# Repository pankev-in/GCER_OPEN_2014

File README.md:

GCER_OPEN_2014
==============

GCER OPEN GAME 2014

Concept:
	-Mechanical:
		two arms, one to hang the hangers on to the Rack,and another one will just attack opponents' side rack

	-Electronic+Controller:
		2 different voltage regulator:
			8V for motors and controller
			5V for Servos
		using Arduino Mega 2560 as the low level communication processor to controll ther hardware
		Raspberry Pi for extential programming tool or other

Game flow:
	1. Robot adjust at frist in the Starting box with hangers on the Robot.
	2. Drive directly to the Side Rack and hang those two hangers on it.
	3. Return to the black tape and turn left to adjust the position.
	4. Drive ahead to the Center Rack and get the other hangers.
	5. Back to Side Rack and put hangers on it.
	... Repeating...
	?. Drive direct to the Opponents' side 
	?. turn around and distroy them XD(Better with some mario musik~).

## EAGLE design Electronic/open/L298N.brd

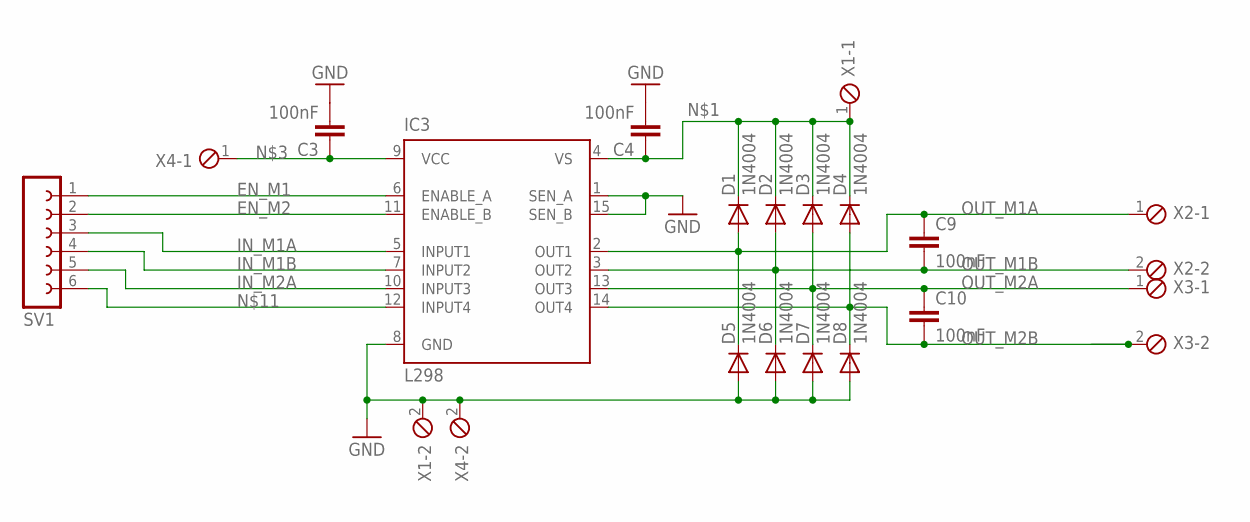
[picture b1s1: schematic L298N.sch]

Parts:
C3, C4, C9, C10: 100nF; C050-050X075
D1, D2, D3, D4, D5, D6, D7, D8: 1N4004; DO41-10
IC3: L298; MULTIWATT-15
SV1: FE06-1; FE06
X1, X2, X3, X4: MPT2; 2POL254

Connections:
EN_M1: IC3.6 (ENABLE_A), SV1.1
EN_M2: IC3.11 (ENABLE_B), SV1.2
GND: C3.2, C4.2, D5.A, D6.A, D7.A, D8.A, IC3.1 (SEN_A), IC3.8 (GND), IC3.15 (SEN_B), X1.2, X4.2
IN_M1A: IC3.5 (INPUT1), SV1.3
IN_M1B: IC3.7 (INPUT2), SV1.4
IN_M2A: IC3.10 (INPUT3), SV1.5
unnamed: C4.1, D1.C, D2.C, D3.C, D4.C, IC3.4 (VS), X1.1
unnamed: C3.1, IC3.9 (VCC), X4.1
unnamed: IC3.12 (INPUT4), SV1.6
OUT_M1A: C9.1, D1.A, D5.C, IC3.2 (OUT1), X2.1
OUT_M1B: C9.2, D2.A, D6.C, IC3.3 (OUT2), X2.2
OUT_M2A: C10.1, D3.A, D7.C, IC3.13 (OUT3), X3.1
OUT_M2B: C10.2, D4.A, D8.C, IC3.14 (OUT4), X3.2

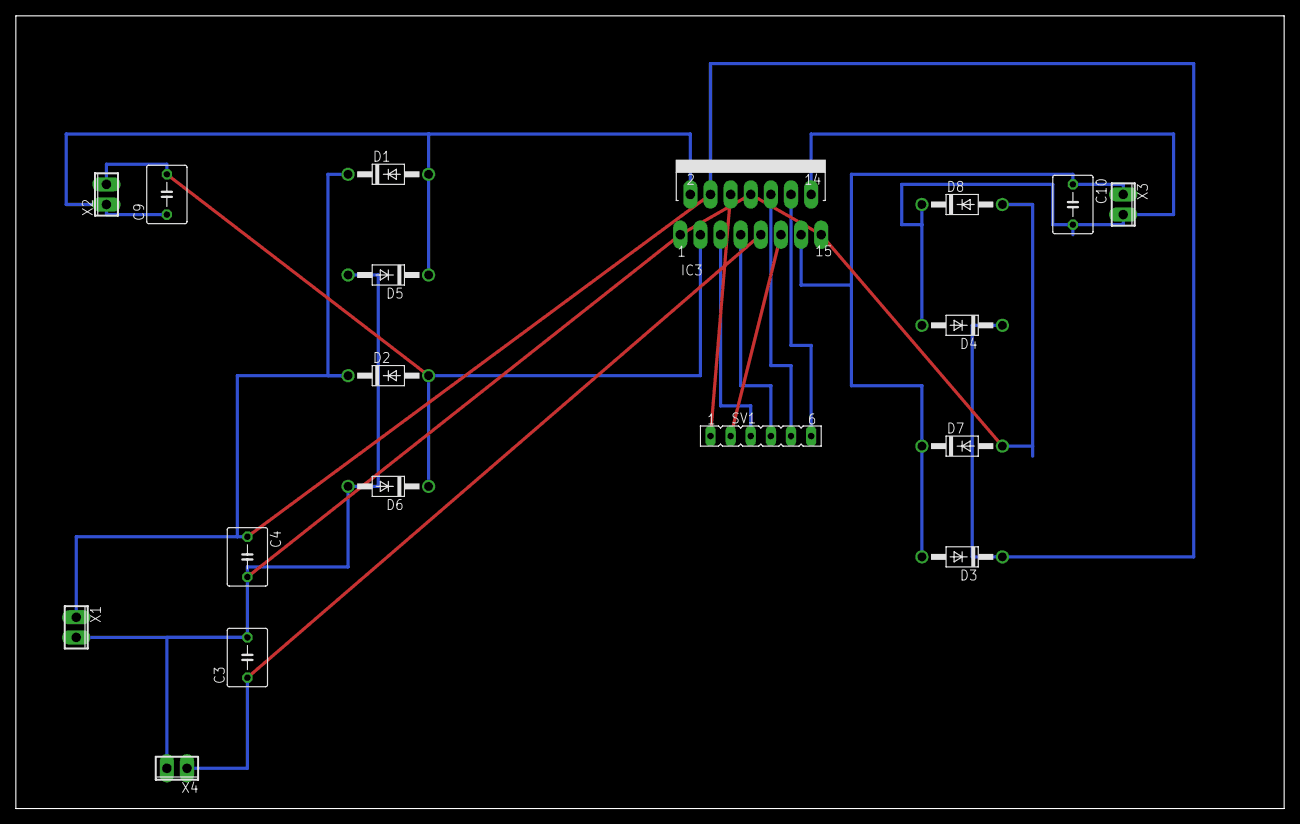
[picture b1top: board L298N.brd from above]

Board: 2 copper layers, 160.0 x 100.0 mm, 18 parts (0 on the bottom side), 13 nets.

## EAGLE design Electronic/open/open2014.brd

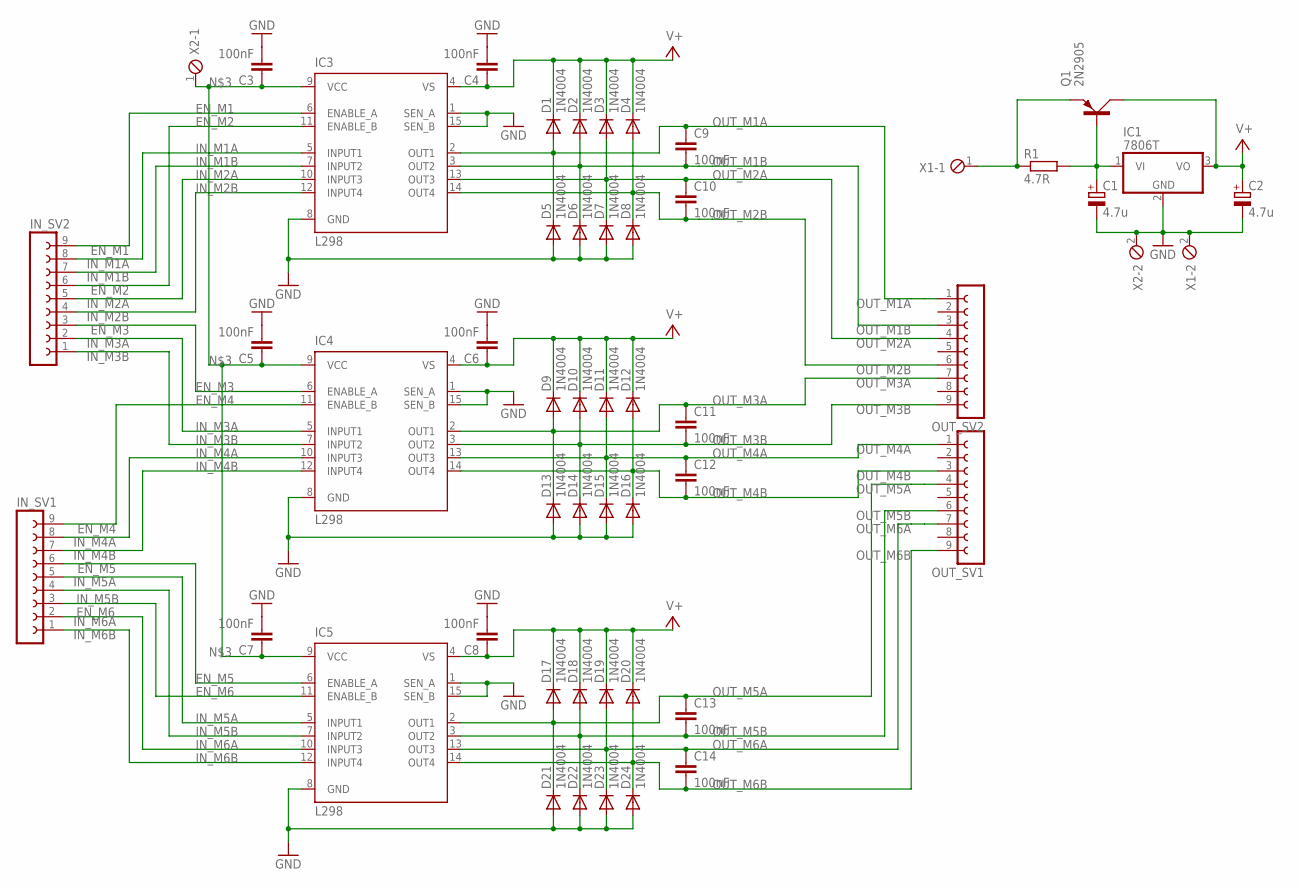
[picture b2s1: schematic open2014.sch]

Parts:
C1, C2: 4.7u; E2,5-6
C3, C4, C5, C6, C7, C8, C9, C10, C11, C12, C13, C14: 100nF; C050-050X075
D1, D2, D3, D4, D5, D6, D7, D8, D9, D10, D11, D12, D13, D14, D15, D16, D17, D18, D19, D20, D21, D22, D23, D24: 1N4004; DO41-10
IC1: 7806T; TO220H
IC3, IC4, IC5: L298; MULTIWATT-15
IN_SV1, IN_SV2: FE09-1; FE09
OUT_SV1, OUT_SV2: FE09-1; FE09
Q1: 2N2905; TO39
R1: 4.7R; 0411/15
X1, X2: MPT2; 2POL254

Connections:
EN_M1: IC3.6 (ENABLE_A), IN_SV2.9
EN_M2: IC3.11 (ENABLE_B), IN_SV2.6
EN_M3: IC4.6 (ENABLE_A), IN_SV2.3
EN_M4: IC4.11 (ENABLE_B), IN_SV1.9
EN_M5: IC5.6 (ENABLE_A), IN_SV1.6
EN_M6: IC5.11 (ENABLE_B), IN_SV1.3
GND: C1.-, C2.-, C3.2, C4.2, C5.2, C6.2, C7.2, C8.2, D5.A, D6.A, D7.A, D8.A, D13.A, D14.A, D15.A, D16.A, D21.A, D22.A, D23.A, D24.A, IC1.2 (GND), IC3.1 (SEN_A), IC3.8 (GND), IC3.15 (SEN_B), IC4.1 (SEN_A), IC4.8 (GND), IC4.15 (SEN_B), IC5.1 (SEN_A), IC5.8 (GND), IC5.15 (SEN_B), X1.2, X2.2
IN_M1A: IC3.5 (INPUT1), IN_SV2.8
IN_M1B: IC3.7 (INPUT2), IN_SV2.7
IN_M2A: IC3.10 (INPUT3), IN_SV2.5
IN_M2B: IC3.12 (INPUT4), IN_SV2.4
IN_M3A: IC4.5 (INPUT1), IN_SV2.2
IN_M3B: IC4.7 (INPUT2), IN_SV2.1
IN_M4A: IC4.10 (INPUT3), IN_SV1.8
IN_M4B: IC4.12 (INPUT4), IN_SV1.7
IN_M5A: IC5.5 (INPUT1), IN_SV1.5
IN_M5B: IC5.7 (INPUT2), IN_SV1.4
IN_M6A: IC5.10 (INPUT3), IN_SV1.2
IN_M6B: IC5.12 (INPUT4), IN_SV1.1
unnamed: Q1.1 (E), R1.1, X1.1
unnamed: C1.+, IC1.1 (VI), Q1.2 (B), R1.2
unnamed: C3.1, C5.1, C7.1, IC3.9 (VCC), IC4.9 (VCC), IC5.9 (VCC), X2.1
OUT_M1A: C9.1, D1.A, D5.C, IC3.2 (OUT1), OUT_SV2.1
OUT_M1B: C9.2, D2.A, D6.C, IC3.3 (OUT2), OUT_SV2.3
OUT_M2A: C10.1, D3.A, D7.C, IC3.13 (OUT3), OUT_SV2.4
OUT_M2B: C10.2, D4.A, D8.C, IC3.14 (OUT4), OUT_SV2.6
OUT_M3A: C11.1, D9.A, D13.C, IC4.2 (OUT1), OUT_SV2.7
OUT_M3B: C11.2, D10.A, D14.C, IC4.3 (OUT2), OUT_SV2.9
OUT_M4A: C12.1, D11.A, D15.C, IC4.13 (OUT3), OUT_SV1.1
OUT_M4B: C12.2, D12.A, D16.C, IC4.14 (OUT4), OUT_SV1.3
OUT_M5A: C13.1, D17.A, D21.C, IC5.2 (OUT1), OUT_SV1.4
OUT_M5B: C13.2, D18.A, D22.C, IC5.3 (OUT2), OUT_SV1.6
OUT_M6A: C14.1, D19.A, D23.C, IC5.13 (OUT3), OUT_SV1.7
OUT_M6B: C14.2, D20.A, D24.C, IC5.14 (OUT4), OUT_SV1.9
V+: C2.+, C4.1, C6.1, C8.1, D1.C, D2.C, D3.C, D4.C, D9.C, D10.C, D11.C, D12.C, D17.C, D18.C, D19.C, D20.C, IC1.3 (VO), IC3.4 (VS), IC4.4 (VS), IC5.4 (VS), Q1.3 (C)

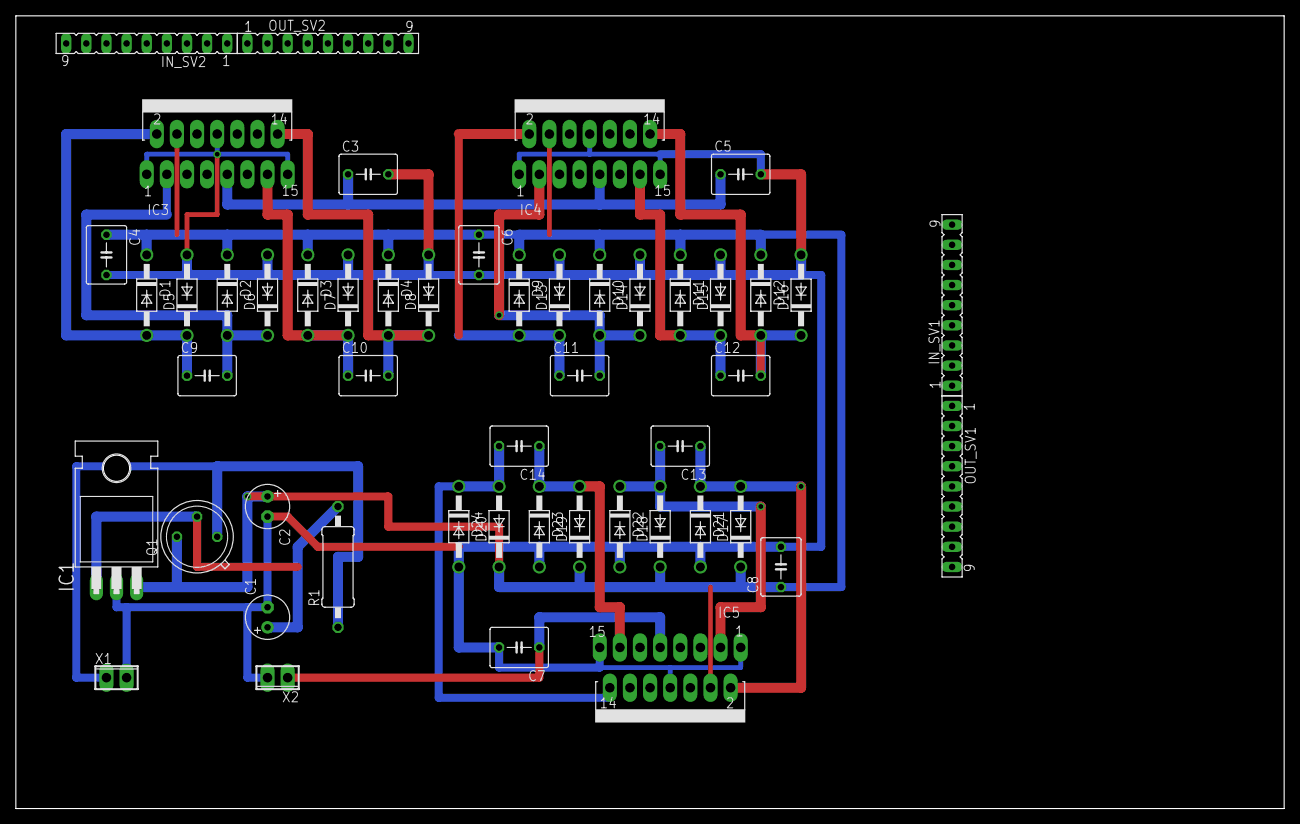
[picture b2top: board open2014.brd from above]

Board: 2 copper layers, 160.0 x 100.0 mm, 50 parts (0 on the bottom side), 35 nets.

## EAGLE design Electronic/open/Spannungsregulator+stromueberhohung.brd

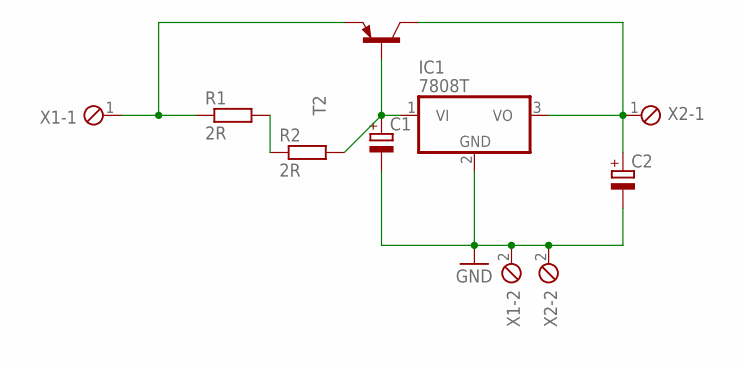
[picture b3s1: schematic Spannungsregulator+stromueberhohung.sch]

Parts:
C1, C2: CPOL-EUE2,5-6E; E2,5-6E
IC1: 7808T; TO220H
R1, R2: 2R; 0204/7
T2: -PNP-TO220V; TO220V
X1, X2: MPT2; 2POL254

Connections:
GND: C1.-, C2.-, IC1.2 (GND), X1.2, X2.2
unnamed: R1.2, R2.1
unnamed: C1.+, IC1.1 (VI), R2.2, T2.1 (B)
unnamed: R1.1, T2.3 (E), X1.1
unnamed: C2.+, IC1.3 (VO), T2.2 (C), X2.1

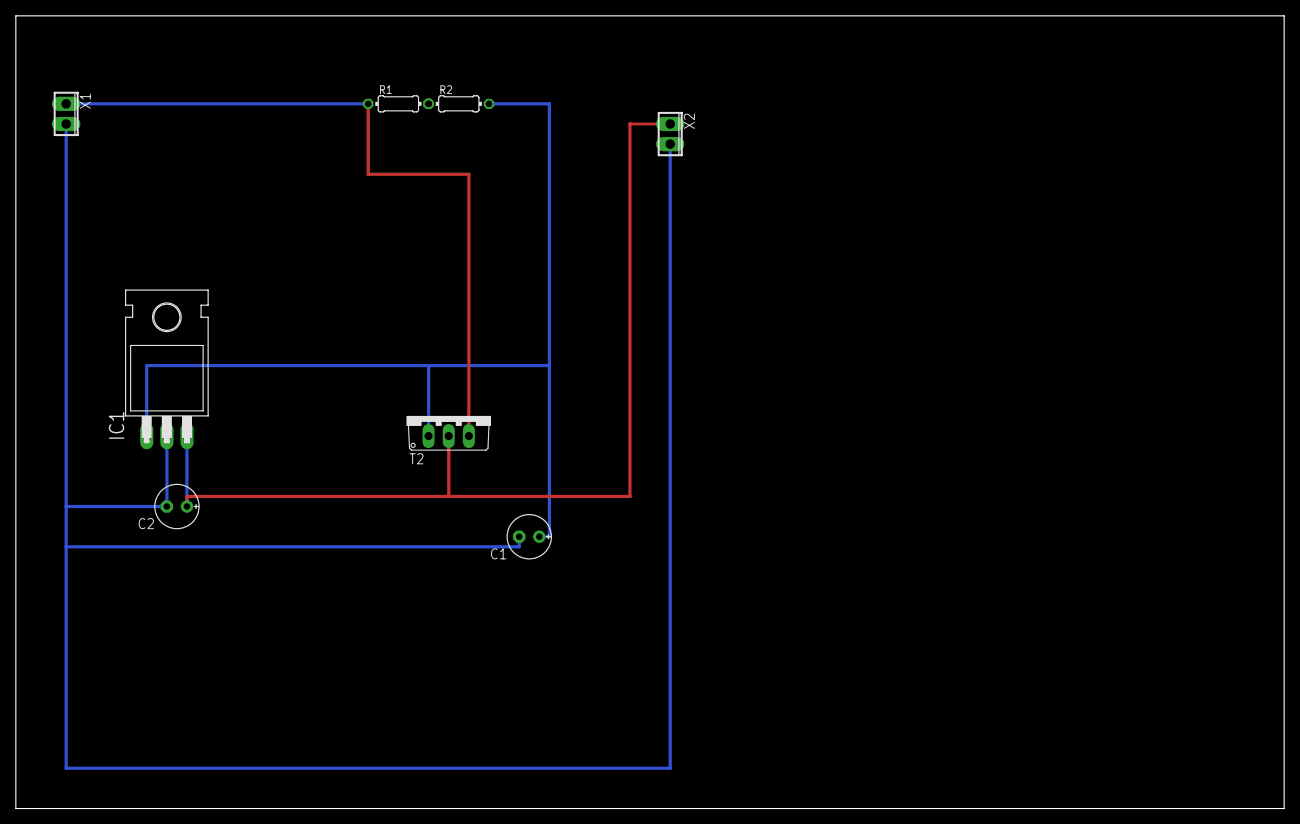
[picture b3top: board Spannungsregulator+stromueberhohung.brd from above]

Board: 2 copper layers, 160.0 x 100.0 mm, 8 parts (0 on the bottom side), 5 nets.

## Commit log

2014-07-07 first Test Programs
    1.Running create with arduino uno
    2.testing H-Bridge controller
2014-07-07 Doku
2014-07-09 create command pdf
2014-07-11 add robot controll library
2014-07-11 implement Servo.cpp and improve Robot
2014-07-11 change directory
2014-07-12 .gitignore
2014-07-13 Added pi ino + start programm
2014-07-13 test changing files
2014-07-14 drive test
2014-07-14 adding lib
2014-07-14 working files
2014-07-14 test
2014-07-14 ADD doUBLE al software
2014-07-14 sdasd
2014-07-14 adasda
2014-07-14 asdasd
2014-07-14 UPLODING-WORKS
2014-07-14 sensor test
2014-07-14 create runs to the front black tape
2014-07-15 runs to the black tape
2014-07-15 Main arm working
2014-07-15 add + tested Motor class
2014-07-15 add Robot_Arm class
    untested yet!
2014-07-17 BIG CHANGES
    cleaning Directory, add test and final program
2014-07-17 Tested-some-methode
2014-07-17 add motorpsoitioning method
2014-07-18 new board
2014-07-18 Test functions
    Only AnglePostion does’t work
2014-07-18 code cleanup
2014-07-18 more code cleanup
2014-07-18 test_pot
2014-07-18 add first robot movements
2014-07-19 Final Setups!!!
    The robot is now ready to be programmed!!!(using Pi+Mega)
2014-07-19 Finail Change before get start!!!!(this time real)
    Add electrical Circuit
    Add Readme, Game flow
2014-07-19 SensorRead_ADD
2014-07-20 MOTORworks
2014-07-20 Changes modified Angleposition method
2014-07-20 Position worksgit add .
2014-07-20 add Python android control server
2014-07-21 asdf
2014-07-21 add moveAll()
2014-07-21 Andriod_Control_Panel
2014-07-24 Los Angeles
2014-07-31 REMOVED EVERYTHING - NEW START
2014-07-31 add hard link
